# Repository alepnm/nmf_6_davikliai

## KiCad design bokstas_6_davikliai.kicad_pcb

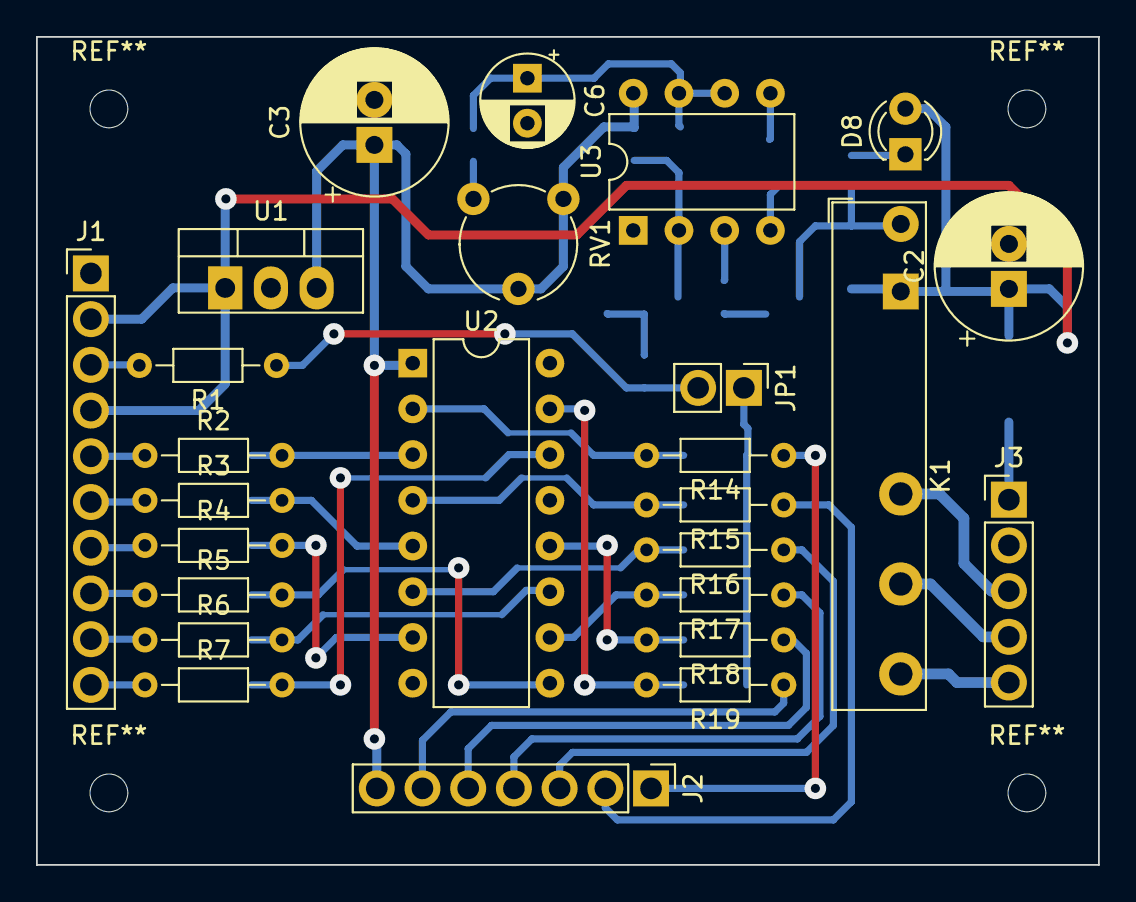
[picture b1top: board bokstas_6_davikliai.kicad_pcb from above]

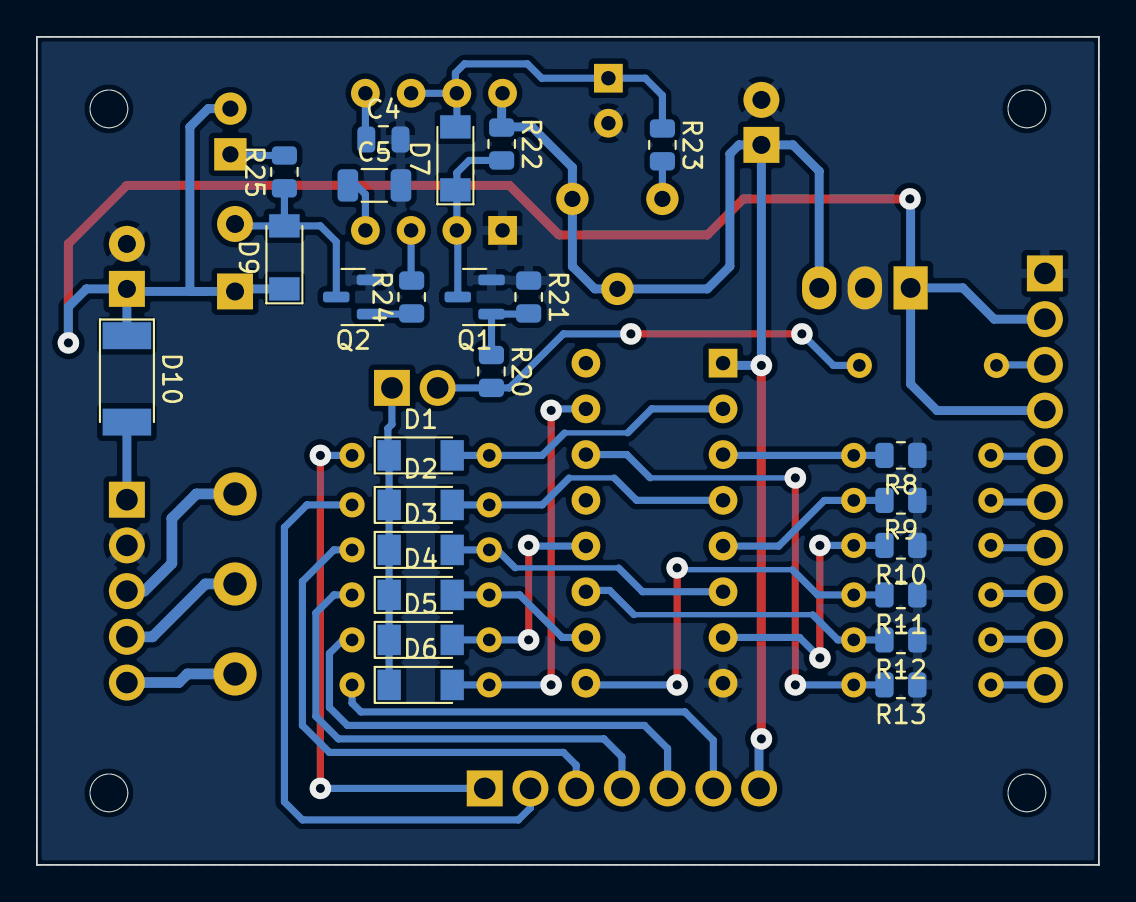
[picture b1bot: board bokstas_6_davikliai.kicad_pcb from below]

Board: 2 copper layers, 59.0 x 46.0 mm, 51 parts (25 on the bottom side), 44 nets.

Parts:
C2: 100x35V; CP_Radial_D8.0mm_P2.50mm
C3: 330x16V; CP_Radial_D8.0mm_P2.50mm
C4: 10n; C_0805_2012Metric
C5: 1uF; C_1206_3216Metric
C6: 10x25V; CP_Radial_D5.0mm_P2.50mm
D1, D2, D3, D4, D5, D6, D7, D9: BAS32; D_MiniMELF
D8: LED; LED_D3.0mm
D10: LL4007; D_MELF
J1: Sensors; PinHeader_1x10_P2.54mm_Vertical
J2: LEDS; PinHeader_1x07_P2.54mm_Vertical
J3: Conn_01x05; PinHeader_1x05_P2.54mm_Vertical
JP1: Jumper_2_Open; PinHeader_1x02_P2.54mm_Vertical
K1: OUT; Relay_SPDT_Finder_34.51_Vertical
Q1, Q2: BC817; SOT-23
R1, R14, R15, R16, R17, R18, R19: 10k; R_Axial_DIN0204_L3.6mm_D1.6mm_P7.62mm_Horizontal
R2, R3, R4, R5, R6, R7: 100k; R_Axial_DIN0204_L3.6mm_D1.6mm_P7.62mm_Horizontal
R8, R9, R10, R11, R12, R13: 100k; R_0805_2012Metric
R20: 1k; R_0805_2012Metric
R21, R22, R24, R25: 10k; R_0805_2012Metric
R23: 51k; R_0805_2012Metric
RV1: 100k; Potentiometer_Piher_PT-6-V_Vertical
U1: L7812; TO-220-3_Vertical
U2: 4049; DIP-16_W7.62mm
U3: NE555P; DIP-8_W7.62mm

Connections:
+12V: C3.1, J2.7, R22.1, RV1.2, RV1.3, U1.3 (OUT), U2.1 (VCC), U3.8 (VCC)
+24V: C2.1, D8.2 (A), D9.1 (K), D10.1 (K), J1.2, J1.4, K1.A1, U1.1 (IN)
/S0: J1.3, R1.2
/S1: J1.5, R2.1
/S2: J1.6, R3.1
/S3: J1.7, R4.1
/S4: J1.8, R5.1
/S5: J1.9, R6.1
/S6: J1.10, R7.1
GND: C2.2, C3.2, C4.2, C5.2, C6.2, J1.1, J3.2, Q1.2 (E), Q2.2 (E), R8.1, R9.1, R10.1, R11.1, R12.1, R13.1, R21.1, U1.2 (GND), U2.8 (VSS), U3.1 (GND)
unnamed: C4.1, U3.5 (CV)
unnamed: C5.1, U3.4 (R)
unnamed: C6.1, D7.2 (A), R23.1, U3.6 (THR), U3.7 (DIS)
unnamed: D1.1 (K), D2.1 (K), D3.1 (K), D4.1 (K), D5.1 (K), D6.1 (K), JP1.1 (A)
unnamed: D1.2 (A), R14.2, U2.2
unnamed: D2.2 (A), R15.2, U2.4
unnamed: D3.2 (A), R16.2, U2.6
unnamed: D4.2 (A), R17.2, U2.10
unnamed: D5.2 (A), R18.2, U2.12
unnamed: D6.2 (A), R19.2, U2.15
unnamed: D7.1 (K), Q1.3 (C), R22.2, U3.2 (TR)
unnamed: D8.1 (K), R25.2
unnamed: D9.2 (A), K1.A2, Q2.3 (C), R25.1
unnamed: D10.2 (A), J3.1
unnamed: J2.1, R14.1
unnamed: J2.2, R15.1
unnamed: J2.3, R16.1
unnamed: J2.4, R17.1
unnamed: J2.5, R18.1
unnamed: J2.6, R19.1
unnamed: J3.3, K1.12
unnamed: J3.4, K1.11
unnamed: J3.5, K1.14
unnamed: JP1.2 (B), R1.1, R20.2
unnamed: Q1.1 (B), R20.1, R21.2
unnamed: Q2.1 (B), R24.1
unnamed: R2.2, R8.2, U2.3
unnamed: R3.2, R9.2, U2.5
unnamed: R4.2, R10.2, U2.7
unnamed: R5.2, R11.2, U2.9
unnamed: R6.2, R12.2, U2.11
unnamed: R7.2, R13.2, U2.14
unnamed: R23.2, RV1.1
unnamed: R24.2, U3.3 (Q)

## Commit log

2022-09-08 init
2022-09-11 versija 1.0
